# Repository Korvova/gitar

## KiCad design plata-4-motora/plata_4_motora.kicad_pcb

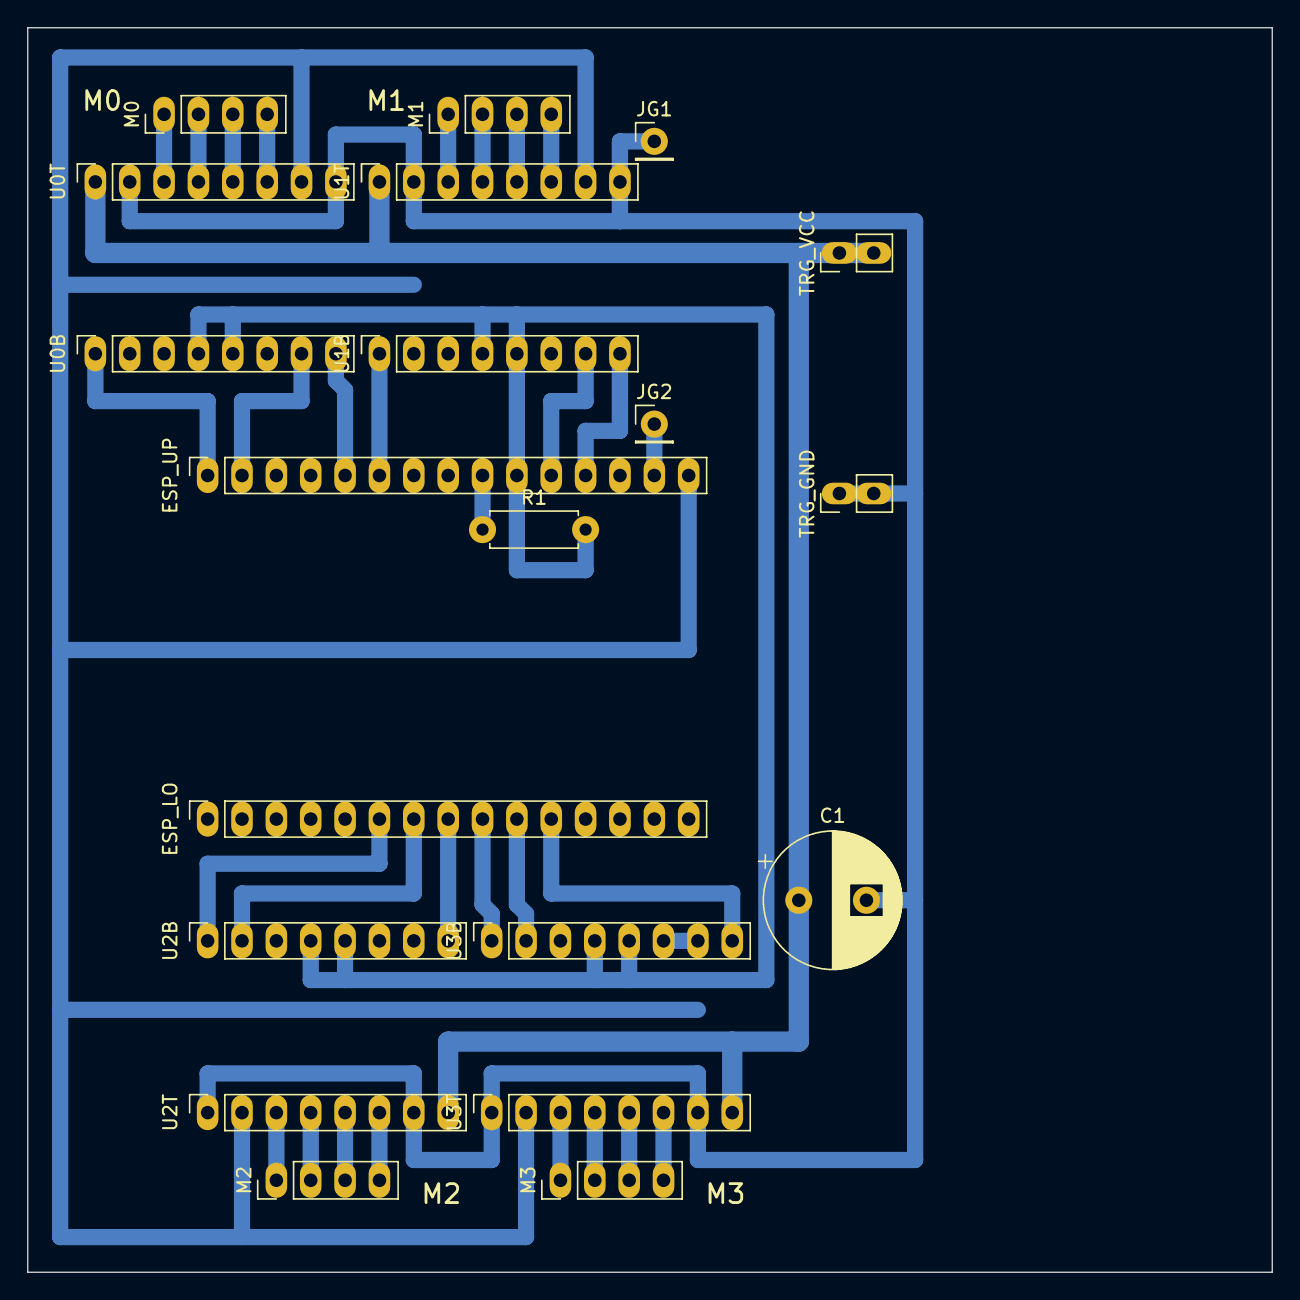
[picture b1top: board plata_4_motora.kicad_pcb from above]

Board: 2 copper layers, 92.0 x 92.0 mm, 26 parts (0 on the bottom side), 33 nets.

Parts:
C1: 470u 35V; CP_Radial_D10.0mm_P5.00mm
DRV0, DRV1, DRV2, DRV3: (no value)
ESP: (no value)
ESP_LO: ESP32 EN..VIN; PinSocket_1x15_P2.54mm_Vertical
ESP_UP: ESP32 D23..3V3; PinSocket_1x15_P2.54mm_Vertical
JG1, JG2: PinHeader_1x01_P2.54mm_Vertical
M0: мотор 0; PinHeader_1x04_P2.54mm_Vertical
M1: мотор 1; PinHeader_1x04_P2.54mm_Vertical
M2: мотор 2; PinHeader_1x04_P2.54mm_Vertical
M3: мотор 3; PinHeader_1x04_P2.54mm_Vertical
R1: 1k; R_Axial_DIN0207_L6.3mm_D2.5mm_P7.62mm_Horizontal
TRG: (no value)
TRG_GND: триггер GND; PinHeader_1x02_P2.54mm_Vertical
TRG_VCC: триггер VCC; PinHeader_1x02_P2.54mm_Vertical
U0B, U0T, U1B, U1T, U2B, U2T, U3B, U3T: S2209; PinSocket_1x08_P2.54mm_Vertical

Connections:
DIR0: ESP_UP.5, U0B.8
DIR1: ESP_UP.12, U1B.8
DIR2: ESP_LO.6, U2B.1
DIR3: ESP_LO.9, U3B.1
EN0: ESP_UP.1, U0B.1
EN1: ESP_UP.6, U1B.1
EN2: ESP_LO.8, U2B.8
EN3: ESP_LO.11, U3B.8
GND: C1.2, ESP_UP.14, JG1.1, JG2.1, TRG_GND.1, TRG_GND.2, U0T.2, U0T.8, U1T.2, U1T.8, U2T.1, U2T.7, U3T.1, U3T.7
M0_A1: M0.2, U0T.4
M0_A2: M0.1, U0T.3
M0_B1: M0.3, U0T.5
M0_B2: M0.4, U0T.6
M1_A1: M1.2, U1T.4
M1_A2: M1.1, U1T.3
M1_B1: M1.3, U1T.5
M1_B2: M1.4, U1T.6
M2_A1: M2.3, U2T.5
M2_A2: M2.4, U2T.6
M2_B1: M2.2, U2T.4
M2_B2: M2.1, U2T.3
M3_A1: M3.3, U3T.5
M3_A2: M3.4, U3T.6
M3_B1: M3.2, U3T.4
M3_B2: M3.1, U3T.3
STEP0: ESP_UP.2, U0B.7
STEP1: ESP_UP.11, U1B.7
STEP2: ESP_LO.7, U2B.2
STEP3: ESP_LO.10, U3B.2
TX2R: ESP_UP.9, R1.1
UART: ESP_UP.10, R1.2, U0B.4, U0B.5, U1B.4, U1B.5, U2B.4, U2B.5, U3B.4, U3B.5
VIO: ESP_UP.15, U0T.7, U1B.2, U1T.7, U2B.6, U2T.2, U3B.6, U3B.7, U3T.2
VM: C1.1, TRG_VCC.1, TRG_VCC.2, U0T.1, U1T.1, U2T.8, U3T.8

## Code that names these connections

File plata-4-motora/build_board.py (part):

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
UP = ["D23", "D22", "TX0", "RX0", "D21", "D19", "D18", "D5", "D17", "D16", "D4", "D2", "D15", "GND", "3V3"]
LO = ["EN", "VP", "VN", "D34", "D35", "D32", "D33", "D25", "D26", "D27", "D14", "D12", "D13", "GND", "VIN"]
PINMAP = {"EN0": "D23", "STEP0": "D22", "DIR0": "D21", "EN1": "D19", "STEP1": "D4", "DIR1": "D2",
          "DIR2": "D32", "STEP2": "D33", "EN2": "D25", "DIR3": "D26", "STEP3": "D27", "EN3": "D14"}

board = pcbnew.NewBoard(OUT)
CU = pcbnew.B_Cu
NET_NAMES = ["VM", "GND", "VIO", "UART", "TX2R"] + list(PINMAP) + \
            ["M%d_%s" % (k, c) for k in range(4) for c in ("A2", "A1", "B1", "B2")]
nets = {}
for n in NET_NAMES:
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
